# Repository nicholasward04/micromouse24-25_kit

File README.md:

The following repository will contain the work I've done as lead of the UCI Micromouse program. Some of the files included are inaccessible shortcuts and are generally administrative in nature. If you would like access please contact me at 818-233-1594 or nnward2004@icloud.com. 

The PCB is iterative and has had 2 other collaborators work on it in previous years. The PCB design was done in KiCAD 7.0 and the STM32 will be programmed using the STM32CubeIDE. I've changed the motor driver to something more capable than the L293D, added a circuit to protect the microcontroller when both the battery and STLINK are being used in full, and added an extra button. The PCB is 4-layer board with 3 GND planes and 1 power plane (split into +5V and +3V3 sections). I rerouted the entire board to fit in the new circuitry while maintaining the legacy aspects of the schematic. 
There are 2 versions of the design, one using an STM32 bluepill and one using solely the STM32F103C8T6 chip. This is to provide the option for teams that are part of the program to route their own boards using either one. 

Below is the relevant schematic.

Version using STM32 Bluepill front and back. The middle 2 layers of the board are mostly empty asides from a few traces and a GND and power plane, and therefore will not be included by image.

Version using STM32F103C8T6 chip front and back. Same as previous in terms of middle 2 layers. 

The software is split into 3 main components:
  1. The simulation
  2. The debugging GUI
  3. The firmware
<br>
1. The first part I worked on was my maze-solving algorithm in mackorone's micromouse simulator (https://github.com/mackorone/mms). Below is a gif of such:

<br>
2. In parallel with the firmware, I developed a debugging tool using the Python Tkinter library, communicating with a UART bluetooth module on board my micromouse. This tool wasn't fully completed, but was useful for viewing telemetry from my mouse, such as IR sensor readings and battery voltage. If I were to do it again, I would have developed it in Visual Studio using C#, since the toolkits are much more advanced and easier to work with. Nevertheless, it was a good experience implementing wireless communication across a UART serial interface. Below is an image of the tool:

<br>
3. Lastly, and most importantly, the firmware for my mouse was devleoped in C using the STM32CubeIDE. Below is a link to my best run at competition, where I placed 4th overall:

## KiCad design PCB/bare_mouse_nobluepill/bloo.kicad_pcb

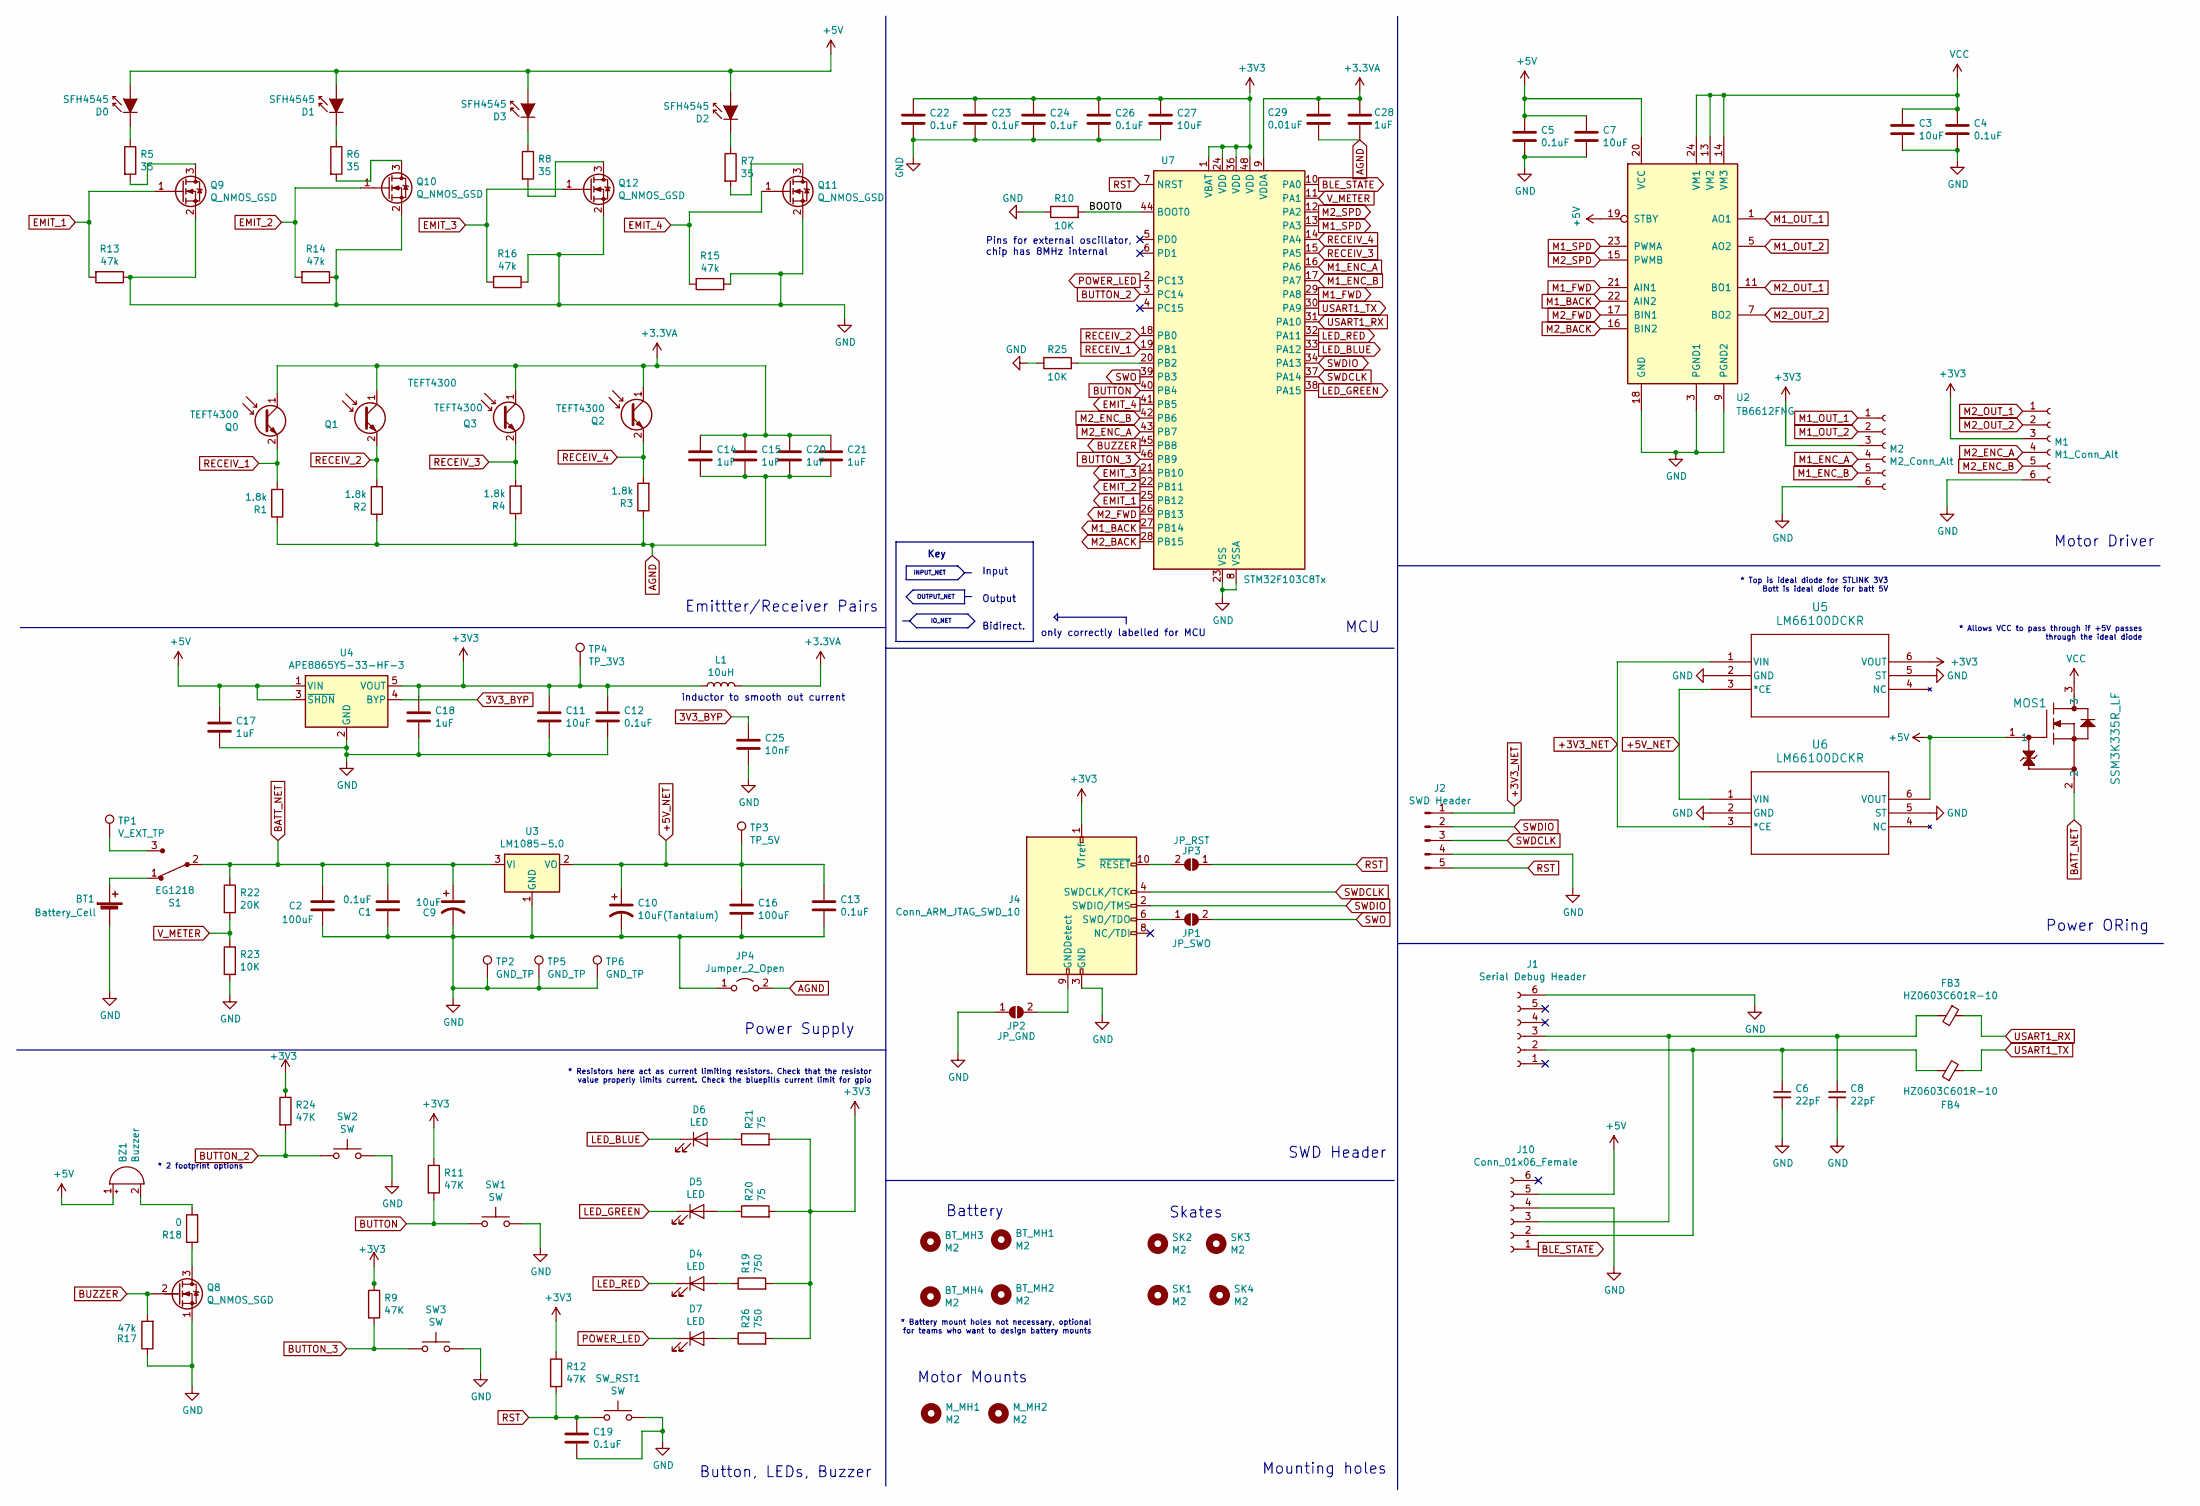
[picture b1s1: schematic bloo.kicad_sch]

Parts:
BT1: Battery_Cell; PinSocket_1x02_P2.54mm_Vertical
BT_MH1, BT_MH2, BT_MH3, BT_MH4: M2; MountingHole_2.2mm_M2
BZ1: Buzzer; MagneticBuzzer_PUI_AT-0927-TT-6-R
C1, C4, C5, C12, C13, C19, C22, C23, C24, C26: 0.1uF; C_1206_3216Metric_Pad1.33x1.80mm_HandSolder
C2, C16: 100uF; CP_Radial_D6.3mm_P2.50mm
C3, C7, C9, C11, C27: 10uF; C_1206_3216Metric_Pad1.33x1.80mm_HandSolder
C6, C8: 22pF; C_0603_1608Metric_Pad1.08x0.95mm_HandSolder
C10: 10uF(Tantalum); C_1206_3216Metric_Pad1.33x1.80mm_HandSolder
C14, C15, C17, C18, C20, C21, C28: 1uF; C_1206_3216Metric_Pad1.33x1.80mm_HandSolder
C25: 10nF; C_1206_3216Metric_Pad1.33x1.80mm_HandSolder
C29: 0.01uF; C_1206_3216Metric_Pad1.33x1.80mm_HandSolder
D0, D1, D2, D3: SFH4545; Emitter
D4, D5, D6, D7: LED; LED_0805_2012Metric_Pad1.15x1.40mm_HandSolder
FB3, FB4: HZ0603C601R-10; R_0603_1608Metric_Pad0.98x0.95mm_HandSolder
J1: Serial Debug Header; PinHeader_1x06_P2.54mm_Vertical
J2: SWD Header; PinHeader_1x05_P2.54mm_Vertical
J4: Conn_ARM_JTAG_SWD_10; PinHeader_2x05_P1.27mm_Vertical
J10: Conn_01x06_Female; PinSocket_1x06_P2.54mm_Vertical
JP1: JP_SWO; SolderJumper-2_P1.3mm_Open_Pad1.0x1.5mm
JP2: JP_GND; SolderJumper-2_P1.3mm_Open_Pad1.0x1.5mm
JP3: JP_RST; SolderJumper-2_P1.3mm_Open_Pad1.0x1.5mm
JP4: Jumper_2_Open; SolderJumper-2_P1.3mm_Bridged_Pad1.0x1.5mm
L1: 10uH; L_1206_3216Metric_Pad1.42x1.75mm_HandSolder
M1: M1_Conn_Alt; Motor Headers
M2: M2_Conn_Alt; Motor Headers
MOS1: SSM3K335R_LF; SOT-23F_TOS
M_MH1, M_MH2: M2; Motor_mouse
Q0, Q1, Q2, Q3: TEFT4300; Emitter
Q8: Q_NMOS_SGD; SOT-23
Q9, Q10, Q11, Q12: Q_NMOS_GSD; SOT-23
R1, R2, R3, R4: 1.8k; R_1206_3216Metric_Pad1.30x1.75mm_HandSolder
R5, R6, R7, R8: 35; R_1206_3216Metric_Pad1.30x1.75mm_HandSolder
R9, R11, R12, R24: 47K; R_1206_3216Metric_Pad1.30x1.75mm_HandSolder
R10, R23, R25: 10K; R_1206_3216Metric_Pad1.30x1.75mm_HandSolder
R13, R14, R15, R16, R17: 47k; R_1206_3216Metric_Pad1.30x1.75mm_HandSolder
R18: 0; R_1206_3216Metric_Pad1.30x1.75mm_HandSolder
R19, R26: 750; R_1206_3216Metric_Pad1.30x1.75mm_HandSolder
R20, R21: 75; R_1206_3216Metric_Pad1.30x1.75mm_HandSolder
R22: 20K; R_1206_3216Metric_Pad1.30x1.75mm_HandSolder
S1: EG1218; MM Switch; MPN EG1218; Digi-Key_PN EG1903-ND
SK1, SK2, SK3, SK4: M2; MountingHole_2.2mm_M2
SW1, SW2, SW3: SW; SW_SPST_REED_CT05-XXXX-G1
SW_RST1: SW; SW_SPST_REED_CT05-XXXX-G1
TP1: V_EXT_TP; PinHeader_1x01_P2.54mm_Vertical
TP2, TP5, TP6: GND_TP; PinHeader_1x01_P2.54mm_Vertical
TP3: TP_5V; PinHeader_1x01_P2.54mm_Vertical
TP4: TP_3V3; PinHeader_1x01_P2.54mm_Vertical
U2: TB6612FNG; SSOP-24_5.3x8.2mm_P0.65mm
U3: LM1085-5.0; 5V Voltage Reg
U4: APE8865Y5-33-HF-3; SOT-23-5
U5, U6: LM66100DCKR; DCK6_TEX
U7: STM32F103C8Tx; LQFP-48_7x7mm_P0.5mm

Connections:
3V3_BYP: C25.1, U4.4 (BYP)
+3.3VA: C14.1, C15.1, C20.1, C21.1, C28.1, C29.1, L1.2, Q0.1 (C), Q1.1 (C), Q2.1 (C), Q3.1 (C), U7.9 (VDDA)
+3V3: C11.1, C12.1, C18.1, C22.1, C23.1, C24.1, C26.1, C27.1, J4.1 (VTref), L1.1, M1.3, M2.3, R9.1, R11.1, R12.1, R19.2, R20.2, R21.2, R24.1, R26.2, TP4.1, U4.5 (VOUT), U5.6 (VOUT), U7.1 (VBAT), U7.24 (VDD), U7.36 (VDD), U7.48 (VDD)
+3V3_NET: J2.1, U5.1 (VIN), U6.3 (*CE)
+5V: BZ1.1 (-), C5.1, C7.1, C17.1, D0.2 (A), D1.2 (A), D2.2 (A), D3.2 (A), J10.5, MOS1.1, U2.19 (STBY), U2.20 (VCC), U4.1 (VIN), U4.3 (~SHDN), U6.6 (VOUT)
+5V_NET: C10.1, C13.1, C16.1, TP3.1, U3.2 (VO), U5.3 (*CE), U6.1 (VIN)
/BOOT0: R10.2, U7.44 (BOOT0)
AGND: C14.2, C15.2, C20.2, C21.2, C28.2, C29.2, JP4.2 (B), R1.1, R2.1, R3.1, R4.1
BLE_STATE: J10.1, U7.10 (PA0)
BUTTON: R11.2, SW1.1, U7.40 (PB4)
BUTTON_2: R24.2, SW2.1, U7.3 (PC14)
BUTTON_3: R9.2, SW3.1, U7.46 (PB9)
BUZZER: Q8.2 (G), R17.2, U7.45 (PB8)
EMIT_1: Q9.1 (G), R13.2, U7.25 (PB12)
EMIT_2: Q10.1 (G), R14.2, U7.22 (PB11)
EMIT_3: Q12.1 (G), R16.2, U7.21 (PB10)
EMIT_4: Q11.1 (G), R15.2, U7.41 (PB5)
GND: BT1.2 (-), C1.1, C2.2, C3.2, C4.2, C5.2, C6.2, C7.2, C8.2, C9.2, C10.2, C11.2, C12.2, C13.2, C16.2, C17.2, C18.2, C19.2, C22.2, C23.2, C24.2, C25.2, C26.2, C27.2, J1.6, J2.4, J4.3 (GND), J4.5 (GND), J10.4, JP2.1 (A), JP4.1 (A), M1.6, M2.6, Q8.1 (S), Q9.2 (S), Q10.2 (S), Q11.2 (S), Q12.2 (S), R10.1, R13.1, R14.1, R15.1, R16.1, R17.1, R23.2, R25.1, SW1.2, SW2.2, SW3.2, SW_RST1.2, TP2.1, TP5.1, TP6.1, U2.3 (PGND1), U2.4 (PGND1), U2.9 (PGND2), U2.10 (PGND2), U2.18 (GND), U3.1 (GND), U4.2 (GND), U5.2 (GND), U5.5 (ST), U6.2 (GND), U6.5 (ST), U7.8 (VSSA), U7.23 (VSS), U7.35 (VSS), U7.47 (VSS); also elsewhere on the board
LED_BLUE: D6.1 (K), U7.33 (PA12)
LED_GREEN: D5.1 (K), U7.38 (PA15)
LED_RED: D4.1 (K), U7.32 (PA11)
M1_BACK: U2.22 (AIN2), U7.27 (PB14)
M1_ENC_A: M2.4, U7.16 (PA6)
M1_ENC_B: M2.5, U7.17 (PA7)
M1_FWD: U2.21 (AIN1), U7.29 (PA8)
M1_OUT_1: M2.1, U2.1 (AO1), U2.2 (AO1)
M1_OUT_2: M2.2, U2.5 (AO2), U2.6 (AO2)
M1_SPD: U2.23 (PWMA), U7.13 (PA3)
M2_BACK: U2.16 (BIN2), U7.28 (PB15)
M2_ENC_A: M1.4, U7.43 (PB7)
M2_ENC_B: M1.5, U7.42 (PB6)
M2_FWD: U2.17 (BIN1), U7.26 (PB13)
M2_OUT_1: M1.1, U2.11 (BO1), U2.12 (BO1)
M2_OUT_2: M1.2, U2.7 (BO2), U2.8 (BO2)
M2_SPD: U2.15 (PWMB), U7.12 (PA2)
unnamed: BT1.1 (+), S1.1
unnamed: BZ1.2 (+), R18.2
unnamed: D0.1 (K), R5.1
unnamed: D1.1 (K), R6.1
unnamed: D2.1 (K), R7.1
unnamed: D3.1 (K), R8.1
unnamed: D4.2 (A), R19.1
unnamed: D5.2 (A), R20.1
unnamed: D6.2 (A), R21.1
unnamed 44: D7.2 (A), R26.1; also elsewhere on the board
unnamed: C6.1, FB4.1, J1.2, J10.2
unnamed: C8.1, FB3.2, J1.3, J10.3
unnamed: J4.9 (GNDDetect), JP2.2 (B)
unnamed: J4.6 (SWO/TDO), JP1.1 (A)
unnamed: J4.10 (~RESET), JP3.2 (B)
unnamed: Q8.3 (D), R18.1
unnamed: Q9.3 (D), R5.2
unnamed: Q10.3 (D), R6.2
unnamed: Q11.3 (D), R7.2
unnamed: Q12.3 (D), R8.2
unnamed: S1.3, TP1.1
unnamed: R25.2, U7.20 (PB2)
POWER_LED: D7.1 (K), U7.2 (PC13); also elsewhere on the board
RECEIV_1: Q0.2 (E), R1.2, U7.19 (PB1)
RECEIV_2: Q1.2 (E), R2.2, U7.18 (PB0)
RECEIV_3: Q3.2 (E), R4.2, U7.15 (PA5)
RECEIV_4: Q2.2 (E), R3.2, U7.14 (PA4)
RST: C19.1, J2.5, JP3.1 (A), R12.2, SW_RST1.1, U7.7 (NRST); also elsewhere on the board
SWDCLK: J2.3, J4.4 (SWDCLK/TCK), U7.37 (PA14)
SWDIO: J2.2, J4.2 (SWDIO/TMS), U7.34 (PA13)
SWO: JP1.2 (B), U7.39 (PB3)
USART1_RX: FB3.1, U7.31 (PA10)
USART1_TX: FB4.2, U7.30 (PA9)
V_METER: R22.2, R23.1, U7.11 (PA1)

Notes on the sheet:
INPUT_NET
Mounting holes
Power ORing
Battery
Input
inductor to smooth out current
* 2 footprint options
* Battery mount holes not necessary, optional for teams who want to design battery mounts
* Top is ideal diode for STLINK 3V3 Bott is ideal diode for batt 5V
Motor Driver
* Allows VCC to pass through if +5V passes through the ideal diode
Emittter/Receiver Pairs
* Resistors here act as current limiting resistors. Check that the resistor value properly limits current. Check the bluepills current limit for gpio
IO_NET
Output
MCU
Key
SWD Header
only correctly labelled for MCU
Motor Mounts
Button, LEDs, Buzzer
Skates
Power Supply
Bidirect.
OUTPUT_NET
Pins for external oscillator, chip has 8MHz internal

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
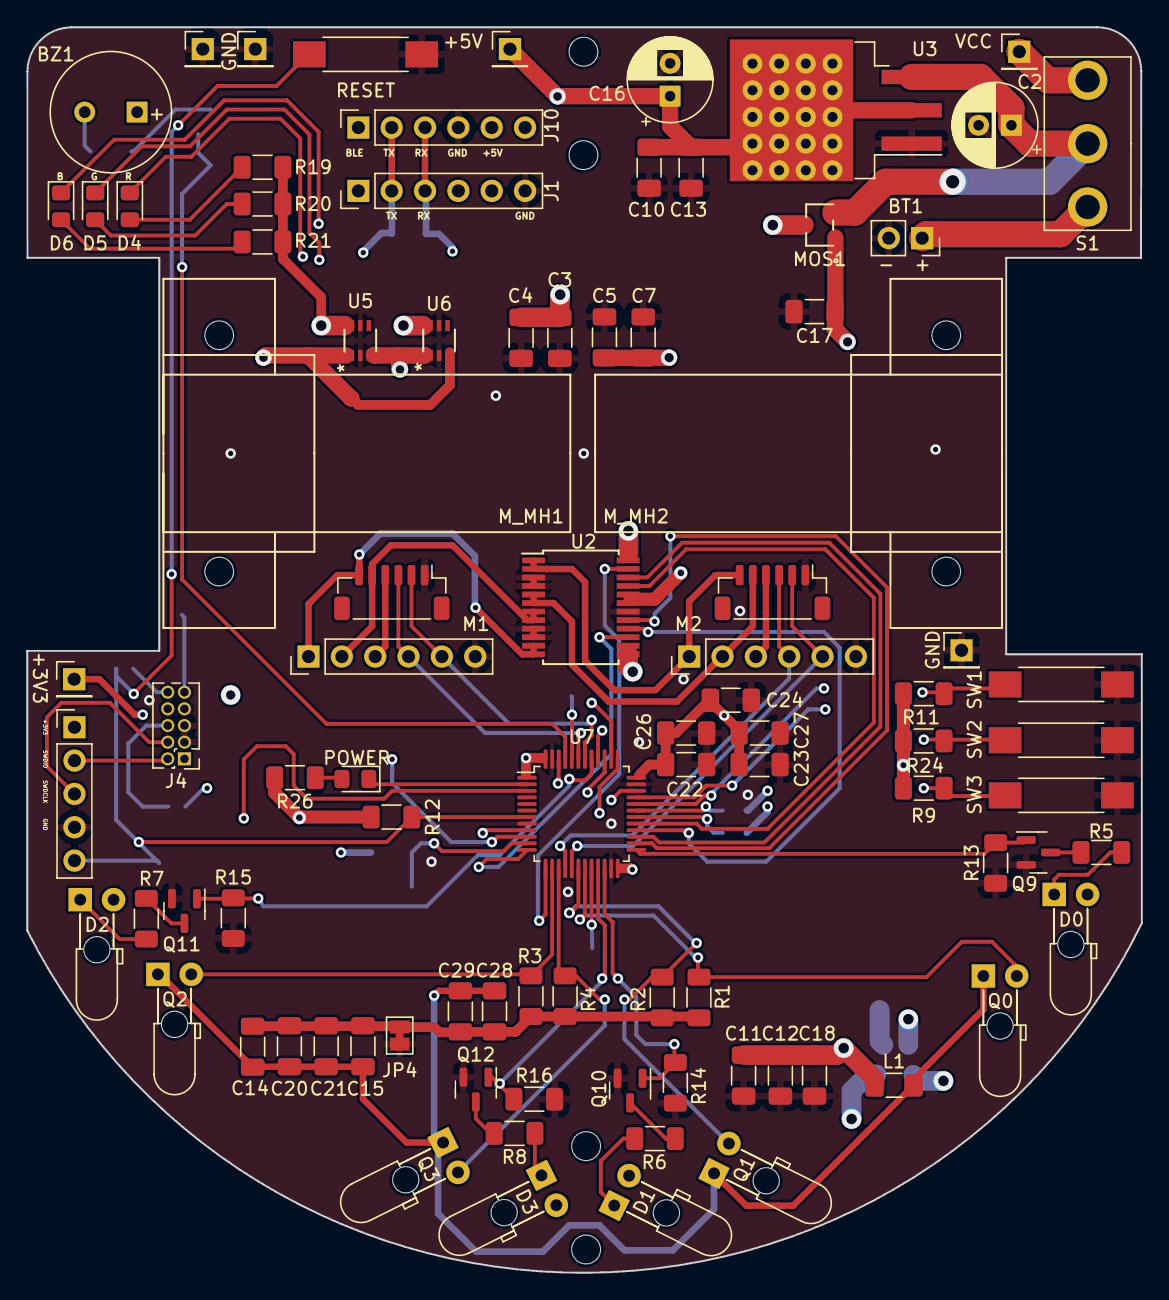
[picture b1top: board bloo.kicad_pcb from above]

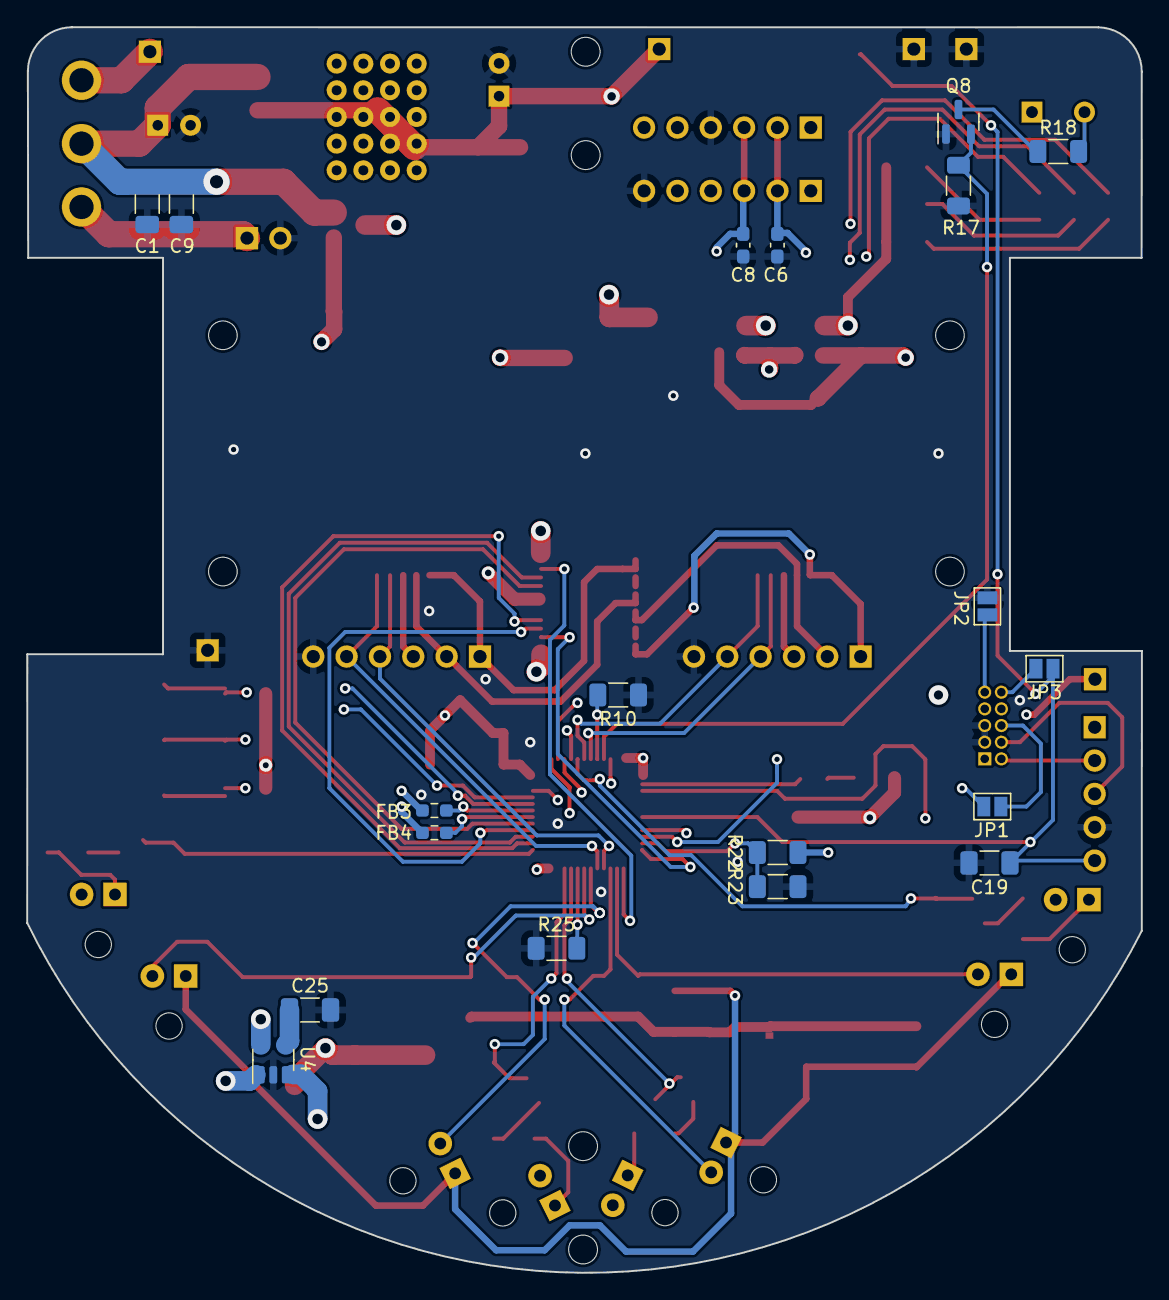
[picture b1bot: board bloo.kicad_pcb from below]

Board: 4 copper layers, 84.9 x 94.9 mm, 111 parts (19 on the bottom side), 71 nets.

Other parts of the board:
POWER: LED; LED_0805_2012Metric_Pad1.15x1.40mm_HandSolder
RESET: SW; SW_SPST_REED_CT05-XXXX-G1

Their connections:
GND: RESET.2; also elsewhere on the board
unnamed 44: POWER.2 (A); also elsewhere on the board
POWER_LED: POWER.1 (K); also elsewhere on the board
RST: RESET.1; also elsewhere on the board

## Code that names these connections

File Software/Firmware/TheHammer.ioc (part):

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Mcu.Name=STM32F103C(8-B)Tx
Mcu.Package=LQFP48
Mcu.UserName=STM32F103C8Tx
PA1.GPIOParameters=GPIO_Label
PA1.GPIO_Label=V_METER
PA1.Signal=ADCx_IN1
PA10.Mode=Asynchronous
PA10.Signal=USART1_RX
PA11.GPIOParameters=PinState,GPIO_Label
PA11.GPIO_Label=LED_Red
PA11.PinState=GPIO_PIN_SET
PA11.Signal=GPIO_Output
PA12.GPIOParameters=PinState,GPIO_Label
PA12.GPIO_Label=LED_Blue
PA12.PinState=GPIO_PIN_SET
PA12.Signal=GPIO_Output
PA13.Mode=Serial_Wire
PA13.Signal=SYS_JTMS-SWDIO
PA14.Mode=Serial_Wire
PA14.Signal=SYS_JTCK-SWCLK
PA15.GPIOParameters=PinState,GPIO_Label
PA15.GPIO_Label=LED_Green
PA15.PinState=GPIO_PIN_SET
PA15.Signal=GPIO_Output
PA2.GPIOParameters=GPIO_Label
PA2.GPIO_Label=ML_PWM
PA2.Signal=S_TIM2_CH3
PA3.GPIOParameters=GPIO_Label
PA3.GPIO_Label=MR_PWM
PA3.Signal=S_TIM2_CH4
PA4.GPIOParameters=GPIO_Label
PA4.GPIO_Label=RECIV_FL
PA4.Signal=ADCx_IN4
PA5.GPIOParameters=GPIO_Label
PA5.GPIO_Label=RECIV_L
PA5.Signal=ADCx_IN5
PA6.GPIOParameters=GPIO_PuPd,GPIO_Label
PA6.GPIO_Label=ML_ENC_A
PA6.GPIO_PuPd=GPIO_NOPULL
PA6.Signal=S_TIM3_CH1
PA7.GPIOParameters=GPIO_PuPd,GPIO_Label
PA7.GPIO_Label=ML_ENC_B
PA7.GPIO_PuPd=GPIO_NOPULL
PA7.Signal=S_TIM3_CH2
PA8.GPIOParameters=GPIO_Label
PA8.GPIO_Label=ML_BWD
PA8.Signal=GPIO_Output
PA9.Mode=Asynchronous
PA9.Signal=USART1_TX
PB0.GPIOParameters=GPIO_Label
PB0.GPIO_Label=RECIV_R
PB0.Signal=ADCx_IN8
PB1.GPIOParameters=GPIO_Label
PB1.GPIO_Label=RECIV_FR
PB1.Signal=ADCx_IN9
PB10.GPIOParameters=GPIO_Label
PB10.GPIO_Label=EMIT_L
PB10.Signal=GPIO_Output
PB11.GPIOParameters=GPIO_Label
PB11.GPIO_Label=EMIT_R
PB11.Signal=GPIO_Output
PB12.GPIOParameters=GPIO_Label
PB12.GPIO_Label=EMIT_FR
PB12.Signal=GPIO_Output
PB13.GPIOParameters=GPIO_Label
PB13.GPIO_Label=MR_FWD
PB13.Signal=GPIO_Output
PB14.GPIOParameters=GPIO_Label
PB14.GPIO_Label=ML_FWD
PB14.Signal=GPIO_Output
PB15.GPIOParameters=GPIO_Label
PB15.GPIO_Label=MR_BWD
PB15.Signal=GPIO_Output
PB4.GPIOParameters=GPIO_Label,GPIO_ModeDefaultEXTI
PB4.GPIO_Label=ARM_SW1
PB4.GPIO_ModeDefaultEXTI=GPIO_MODE_IT_FALLING
PB4.Signal=GPXTI4
PB5.GPIOParameters=GPIO_Label
PB5.GPIO_Label=EMIT_FL
PB5.Signal=GPIO_Output
PB6.GPIOParameters=GPIO_Label
PB6.GPIO_Label=MR_ENC_B
PB6.Signal=S_TIM4_CH1
PB7.GPIOParameters=GPIO_Label
PB7.GPIO_Label=MR_ENC_A
PB7.Signal=S_TIM4_CH2
PB8.GPIOParameters=GPIO_Label
PB8.GPIO_Label=BUZZER
PB8.Signal=GPIO_Output
PB9.GPIOParameters=GPIO_Label
PB9.GPIO_Label=LOADMAZE_SW3
PB9.Signal=GPIO_Input
PC13-TAMPER-RTC.GPIOParameters=GPIO_Label
PC13-TAMPER-RTC.GPIO_Label=LED_Power
PC13-TAMPER-RTC.Signal=GPIO_Output
PC14-OSC32_IN.GPIOParameters=GPIO_Label,GPIO_ModeDefaultEXTI
PC14-OSC32_IN.GPIO_Label=RACE_SW2
PC14-OSC32_IN.GPIO_ModeDefaultEXTI=GPIO_MODE_IT_FALLING
PC14-OSC32_IN.Signal=GPXTI14
RCC.SYSCLKFreq_VALUE=36000000
RCC.SYSCLKSource=RCC_SYSCLKSOURCE_PLLCLK
board=custom

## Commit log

2024-06-19 Initialized file layout, added schedules
2024-06-30 Added base file to directory, imported custom symbols
2024-06-30 Updated BOM with changes associated with motor driver and removal of 100k resistors
2024-06-30 Added button, updated BOM
2024-07-13 Current state
2024-07-14 Added power ORing schematic. Updated BOM and added footprints/symbols
2024-07-18 Removed notes
2024-07-24 Created second kicad directory for version of micromouse without bluepill (using solely STM chip). Updated BOM accordingly and updated schematic for said file
2024-07-26 Reviewed and updated schematics accordingly, updated BOM, created PCB Design Notes
2024-08-01 Completed routing for version using bluepill, no DRC errors. Began routing for version with no bluepill
2024-08-04 Completed routing of non-bluepill version of schematic. All DRC errors cleared. Version/Name/Year label updated. To be reviewed.
2024-08-07 Adjusted dielectric stackup thickness to 1.6mm. Both PCBs have been reviewed, TB manufactured.
2024-08-08 Updated silkscreen, generated gerber and drill files. Placed PCB orders.
2024-08-17 Added shortcut to soldering checklist. All parts received, begin testing of new mouse
2024-08-23 Added schematic PDF
2024-09-17 Added WIP logo for 24-25, awaiting approval or requests to change for logo
2024-09-18 Added fliers
2024-11-15 Updated bluepill version of mouse to use L293D motor driver rather than TB6612FNG
2024-11-15 Added API.cpp, API.h from mackarone micromouse simulator. Created main file and created layout based on my previous software
2024-11-15 Completed setGoalCell function
2024-11-16 Completed scanWalls, scanWallsAdjacent functions
2024-11-24 Completed Floodfill function
2024-11-24 Finished bestCell function
2024-11-24 Finished getNeighborCells function
2024-11-24 Finished main function and auxillary mazeInit function
2024-11-24 Discovered bug with scanWalls and scanWallsAdjacent - Need to debug
2024-12-13 Resolved sim update errors, completed maze solving sim algorithm
2025-02-22 Added interrupt for UART communication across bluetooth link. Configured clock settings in IOC to use internal clock.
2025-02-23 Added mm_commands files for implementation of UART command parsing and data transmit
2025-02-27 Added directory and file outline for Bluetooth communication and GUI. Started creating GUI using tkinter, not currently functional.
2025-02-28 Added essential functionality to GUI. Added expadnable command parsing. Added fit to window frames.
2025-02-28 Added data field to data frame. Created file for maze translation. Implemented regular calls to listen for data and update accordingly.
2025-03-01 Unstable
2025-03-02 Implemented pair, disconnect, send, receive using pyserial. Began implementation of debug mode and PAIRED command. Currently unstable
2025-03-03 Debug data parsing working. ACK for set mode to turn off working.
2025-03-04 Implemented rest of current commands on client side. Implemented maze file creation. New commands untested.
2025-03-07 If paired receives no response, updates GUI and disconnects socket
2025-03-07 Fixed packet alignment for 24 byte packets.
2025-03-08 Completed maze translation scheme. File write back can still be improved to be correctly visualized in file, but works when loaded into GUI.
2025-03-10 Added raw IR values to debug packet. Untested
2025-03-25 Fixed formatting of IR byte data.
2025-04-02 Added mouse state struct to hold debug information. Implemented low level motor control software, modified IOC accordingly.
2025-04-04 Experimental encoder code. Not working currently.
2025-04-05 Encoders working. RPM calculation tested.
2025-04-14 Integrated floodfill module into firmware package. Implemented button functionality. Fixed encoder ticking in wrong direction.
2025-05-13 Wrote bulk of profile code. Calibrated battery readings and PWM outputs.
2025-05-15 Tuned constants. Added blocks for steering adjustments.
2025-05-17 Tuned constants.
2025-05-18 Bug fixes. Implemented search mode. Currently doesn't build.
2025-05-19 Updated profiles. Unstable.
2025-05-20 Implemented non-smooth turns. Unstable, could be because low battery voltage and variable lighting. Rotational and positional controller need tuning. Floodfill unstable, could have incorrect walls be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
2025-05-21 Normal turns. Non smooth motion. Fixed 180 for return to start position. Unstable.
2025-05-23 Tuned values. Modified how parameters are packed and passed for profiles. Began work on race mode in simulator <- unstable.
2025-05-24 Completed race mode in sim and firmware. Added save/load maze from flash. Changed parameter struct and packing.
2025-05-25 Final tuning and changes before competition.
2025-05-25 Real final commit. Tuned values. Fixed enter goal, fixed start after full run completion.
2025-05-26 Removed remnants of feedforward. Fixed spelling errors.
2025-09-07 Media files
